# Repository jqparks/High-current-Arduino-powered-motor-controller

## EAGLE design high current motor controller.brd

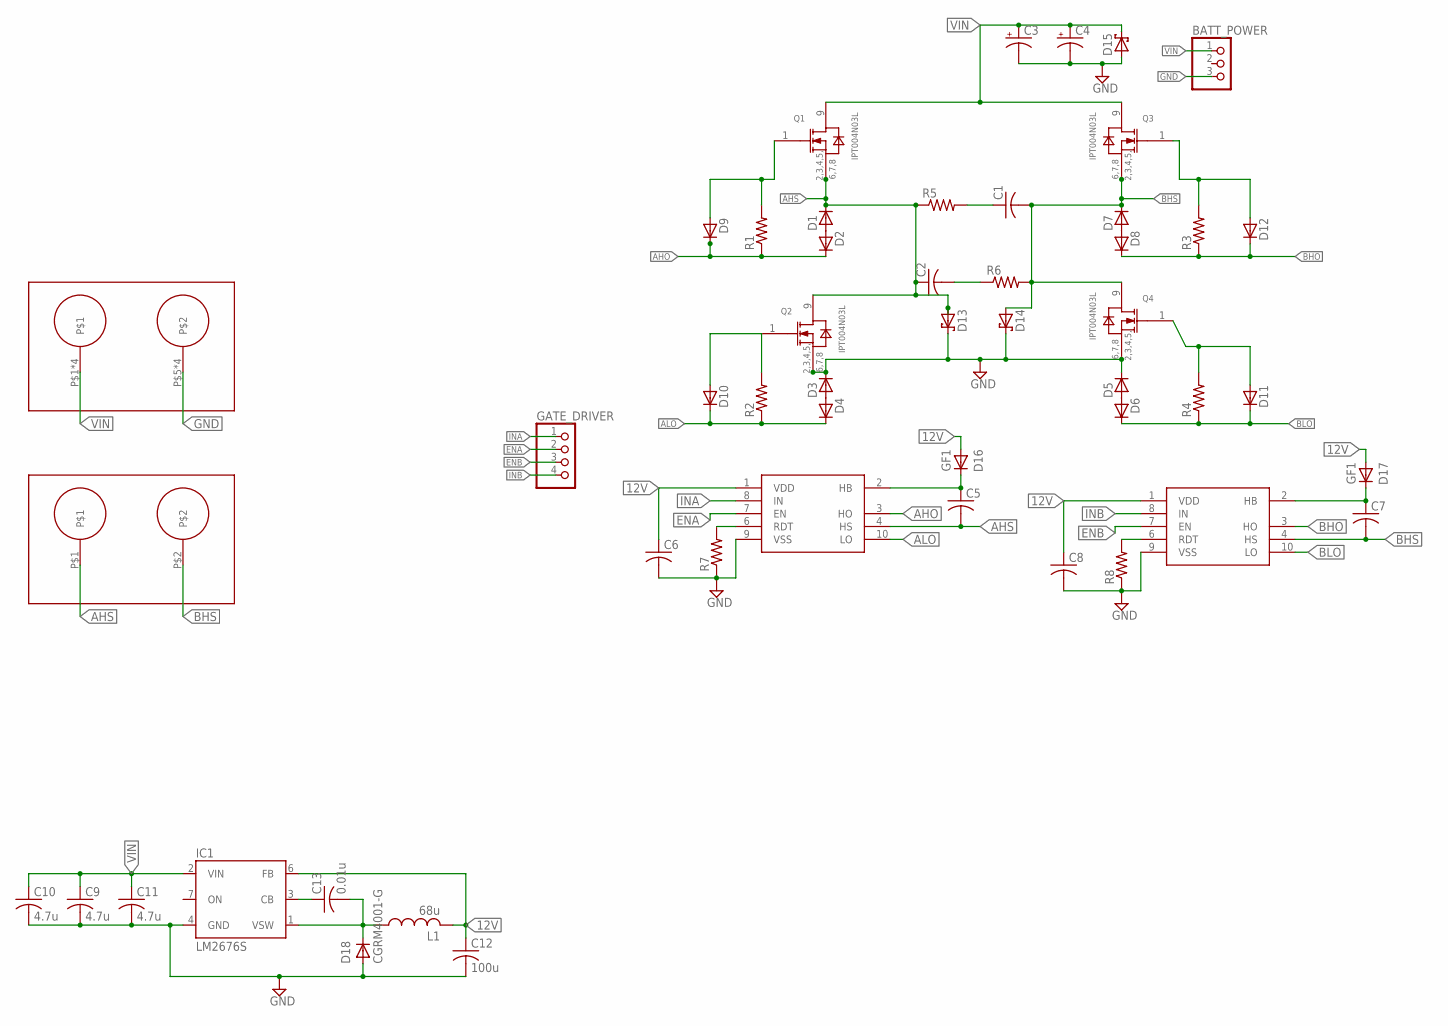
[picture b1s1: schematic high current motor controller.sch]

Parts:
BATT_POWER: PINHD-1X3; 1X03
C1, C2, C5, C6, C7, C8: C-USC0805; C0805
C3, C4: CPOL-USE5-13; E5-13
C9, C10, C11: 4.7u; C0805
C12: 100u; C0805
C13: 0.01u; C0805
D1, D2, D3, D4, D5, D6, D7, D8, D9, D10, D11, D12: D-SOD123; SOD123
D13, D14, D15: SCHOTTKY-DIODESMC; SMC
D16, D17: GF1; SMA-DO214AC
D18: CGRM4001-G; SMA-DO214AC
GATE_DRIVER: PINHD-1X4; 1X04
IC1: LM2676S; TO263-7
L1: 68u; L_WURTH_7447709680
Q1, Q2, Q3, Q4: IPT004N03L; INF-PG-HSOF-8-1-0
R1, R2, R3, R4, R5, R6, R7, R8: R-US_M0805; M0805
U$1, U$2: LM5106MM; MSOP10
U$3: TE_2PIN_125A; TE_125A
U$4: MOLEX_2PIN_50A; MOLEX_50A

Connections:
12V: C6.1, C8.1, C12.1, D16.A, D17.A, IC1.6 (FB), L1.P$2 (2), U$1.1 (VDD), U$2.1 (VDD)
AHO: D2.1 (C), D9.1 (C), R1.1, U$1.3 (HO)
AHS: C2.1, C5.2, D1.1 (C), D13.A, Q1.2, Q1.3, Q1.4, Q1.5, Q1.6, Q1.7, Q1.8, Q2.9, R5.1, U$1.4 (HS), U$4.P$1
ALO: D4.1 (C), D10.1 (C), R2.1, U$1.10 (LO)
BHO: D8.1 (C), D12.1 (C), R3.1, U$2.3 (HO)
BHS: C1.2, C7.2, D7.1 (C), D14.A, Q3.2, Q3.3, Q3.4, Q3.5, Q3.6, Q3.7, Q3.8, Q4.9, R6.2, U$2.4 (HS), U$4.P$2
BLO: D6.1 (C), D11.1 (C), R4.1, U$2.10 (LO)
ENA: GATE_DRIVER.2, U$1.7 (EN)
ENB: GATE_DRIVER.3, U$2.7 (EN)
GND: BATT_POWER.3, C3.-, C4.-, C6.2, C8.2, C9.2, C10.2, C11.2, C12.2, D3.1 (C), D5.1 (C), D13.C, D14.C, D15.A, D18.A, IC1.4 (GND), Q2.2, Q2.3, Q2.4, Q2.5, Q2.6, Q2.7, Q2.8, Q4.2, Q4.3, Q4.4, Q4.5, Q4.6, Q4.7, Q4.8, R7.1, R8.1, U$1.9 (VSS), U$2.9 (VSS), U$3.P$5, U$3.P$6, U$3.P$7, U$3.P$8
INA: GATE_DRIVER.1, U$1.8 (IN)
INB: GATE_DRIVER.4, U$2.8 (IN)
unnamed: D1.2 (A), D2.2 (A)
unnamed: R8.2, U$2.6 (RDT)
unnamed: R7.2, U$1.6 (RDT)
unnamed: C1.1, R5.2
unnamed: C7.1, D17.K (C), U$2.2 (HB)
unnamed: D7.2 (A), D8.2 (A)
unnamed: C5.1, D16.K (C), U$1.2 (HB)
unnamed: D10.2 (A), Q2.1, R2.2
unnamed: C2.2, R6.1
unnamed: D3.2 (A), D4.2 (A)
unnamed: D5.2 (A), D6.2 (A)
unnamed: D9.2 (A), Q1.1, R1.2
unnamed: D12.2 (A), Q3.1, R3.2
unnamed: C13.1, IC1.3 (CB)
unnamed: C13.2, D18.K (C), IC1.1 (VSW), L1.P$1 (1)
unnamed: D11.2 (A), Q4.1, R4.2
VIN: BATT_POWER.1, C3.+, C4.+, C9.1, C10.1, C11.1, D15.C, IC1.2 (VIN), Q1.9, Q3.9, U$3.P$1, U$3.P$1.1, U$3.P$1.2, U$3.P$1.3

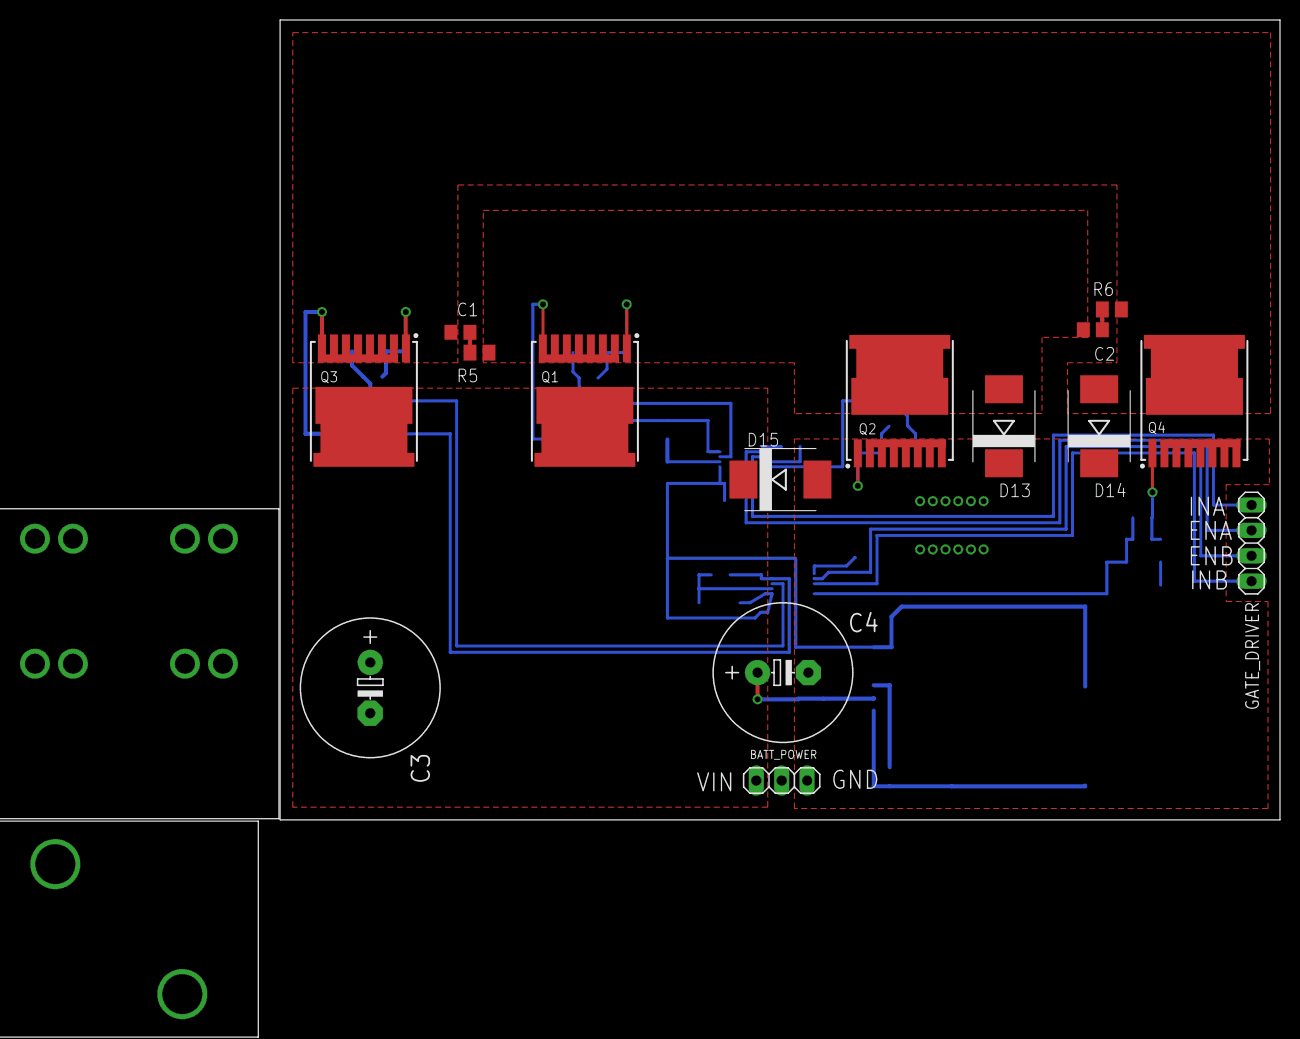
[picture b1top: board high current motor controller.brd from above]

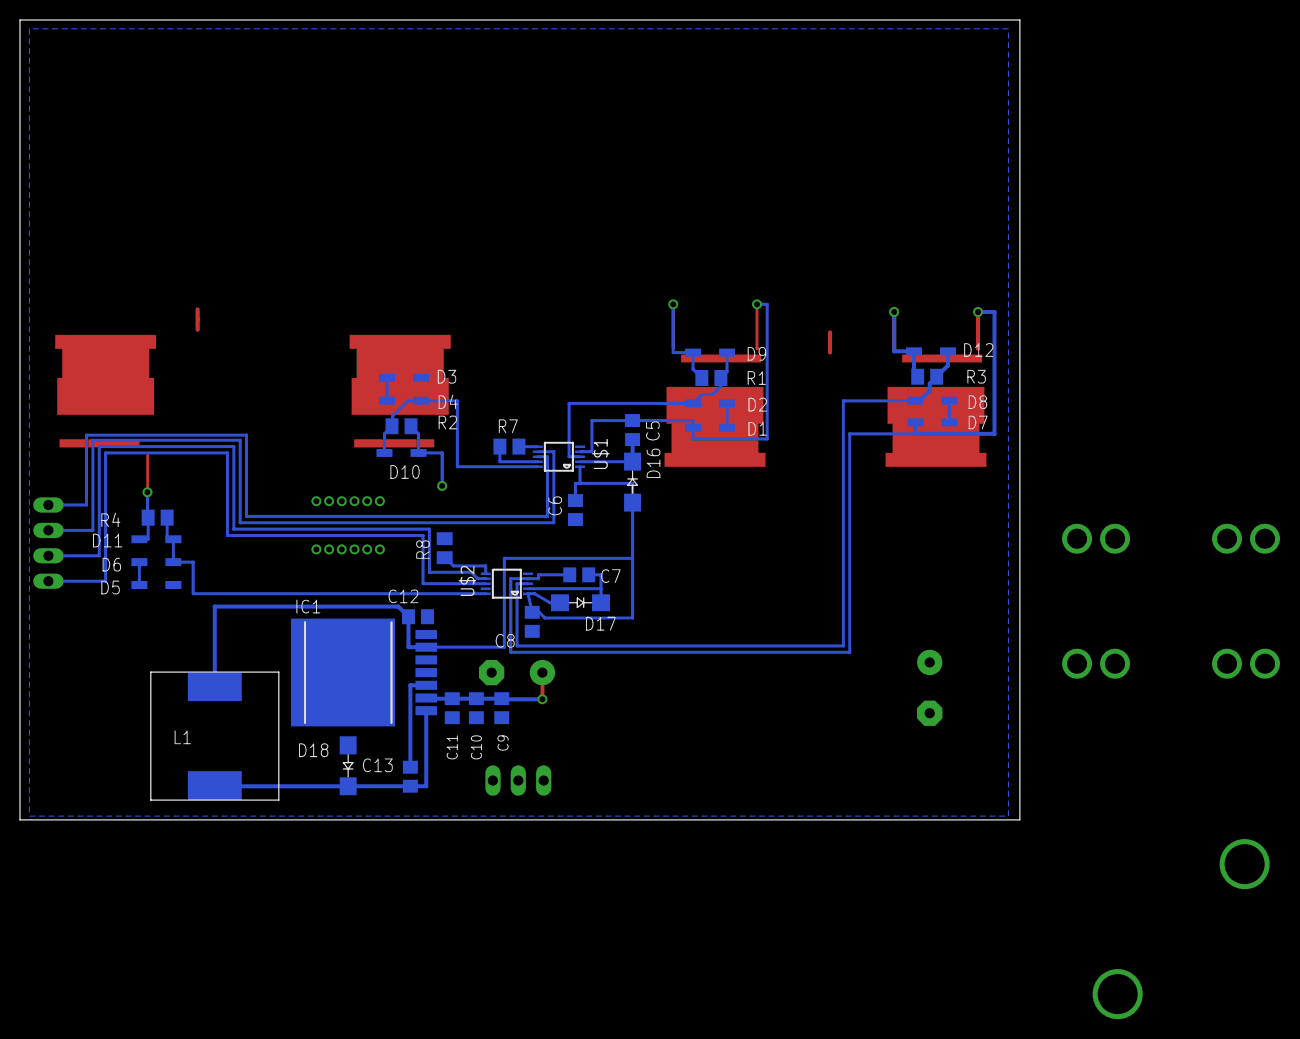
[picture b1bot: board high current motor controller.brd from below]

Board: 2 copper layers, 100.0 x 80.0 mm, 51 parts (34 on the bottom side), 29 nets.

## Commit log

2016-07-01 Add gerber and schematics
2016-07-01 Fixed silk screen overlapping with pads
2016-07-02 Add power and signal terminal blocks
2016-07-02 Add switching regulator to transform battery voltage to 12V
2016-07-02 Fixed regulator layout. TODO:Select values for regulator components
2016-07-02 Fixed silk screen overlap errors and selected values for regulator components TODO:Find corrent footprints for regulator components
2016-07-14 Switching regulator components updated with correct values and packages
2016-07-19 Moved 12V regulator
2016-07-20 Added library for power and motor connectors; updated schematic with connectors
2016-07-20 Updated connector library to use all pads of power connector
